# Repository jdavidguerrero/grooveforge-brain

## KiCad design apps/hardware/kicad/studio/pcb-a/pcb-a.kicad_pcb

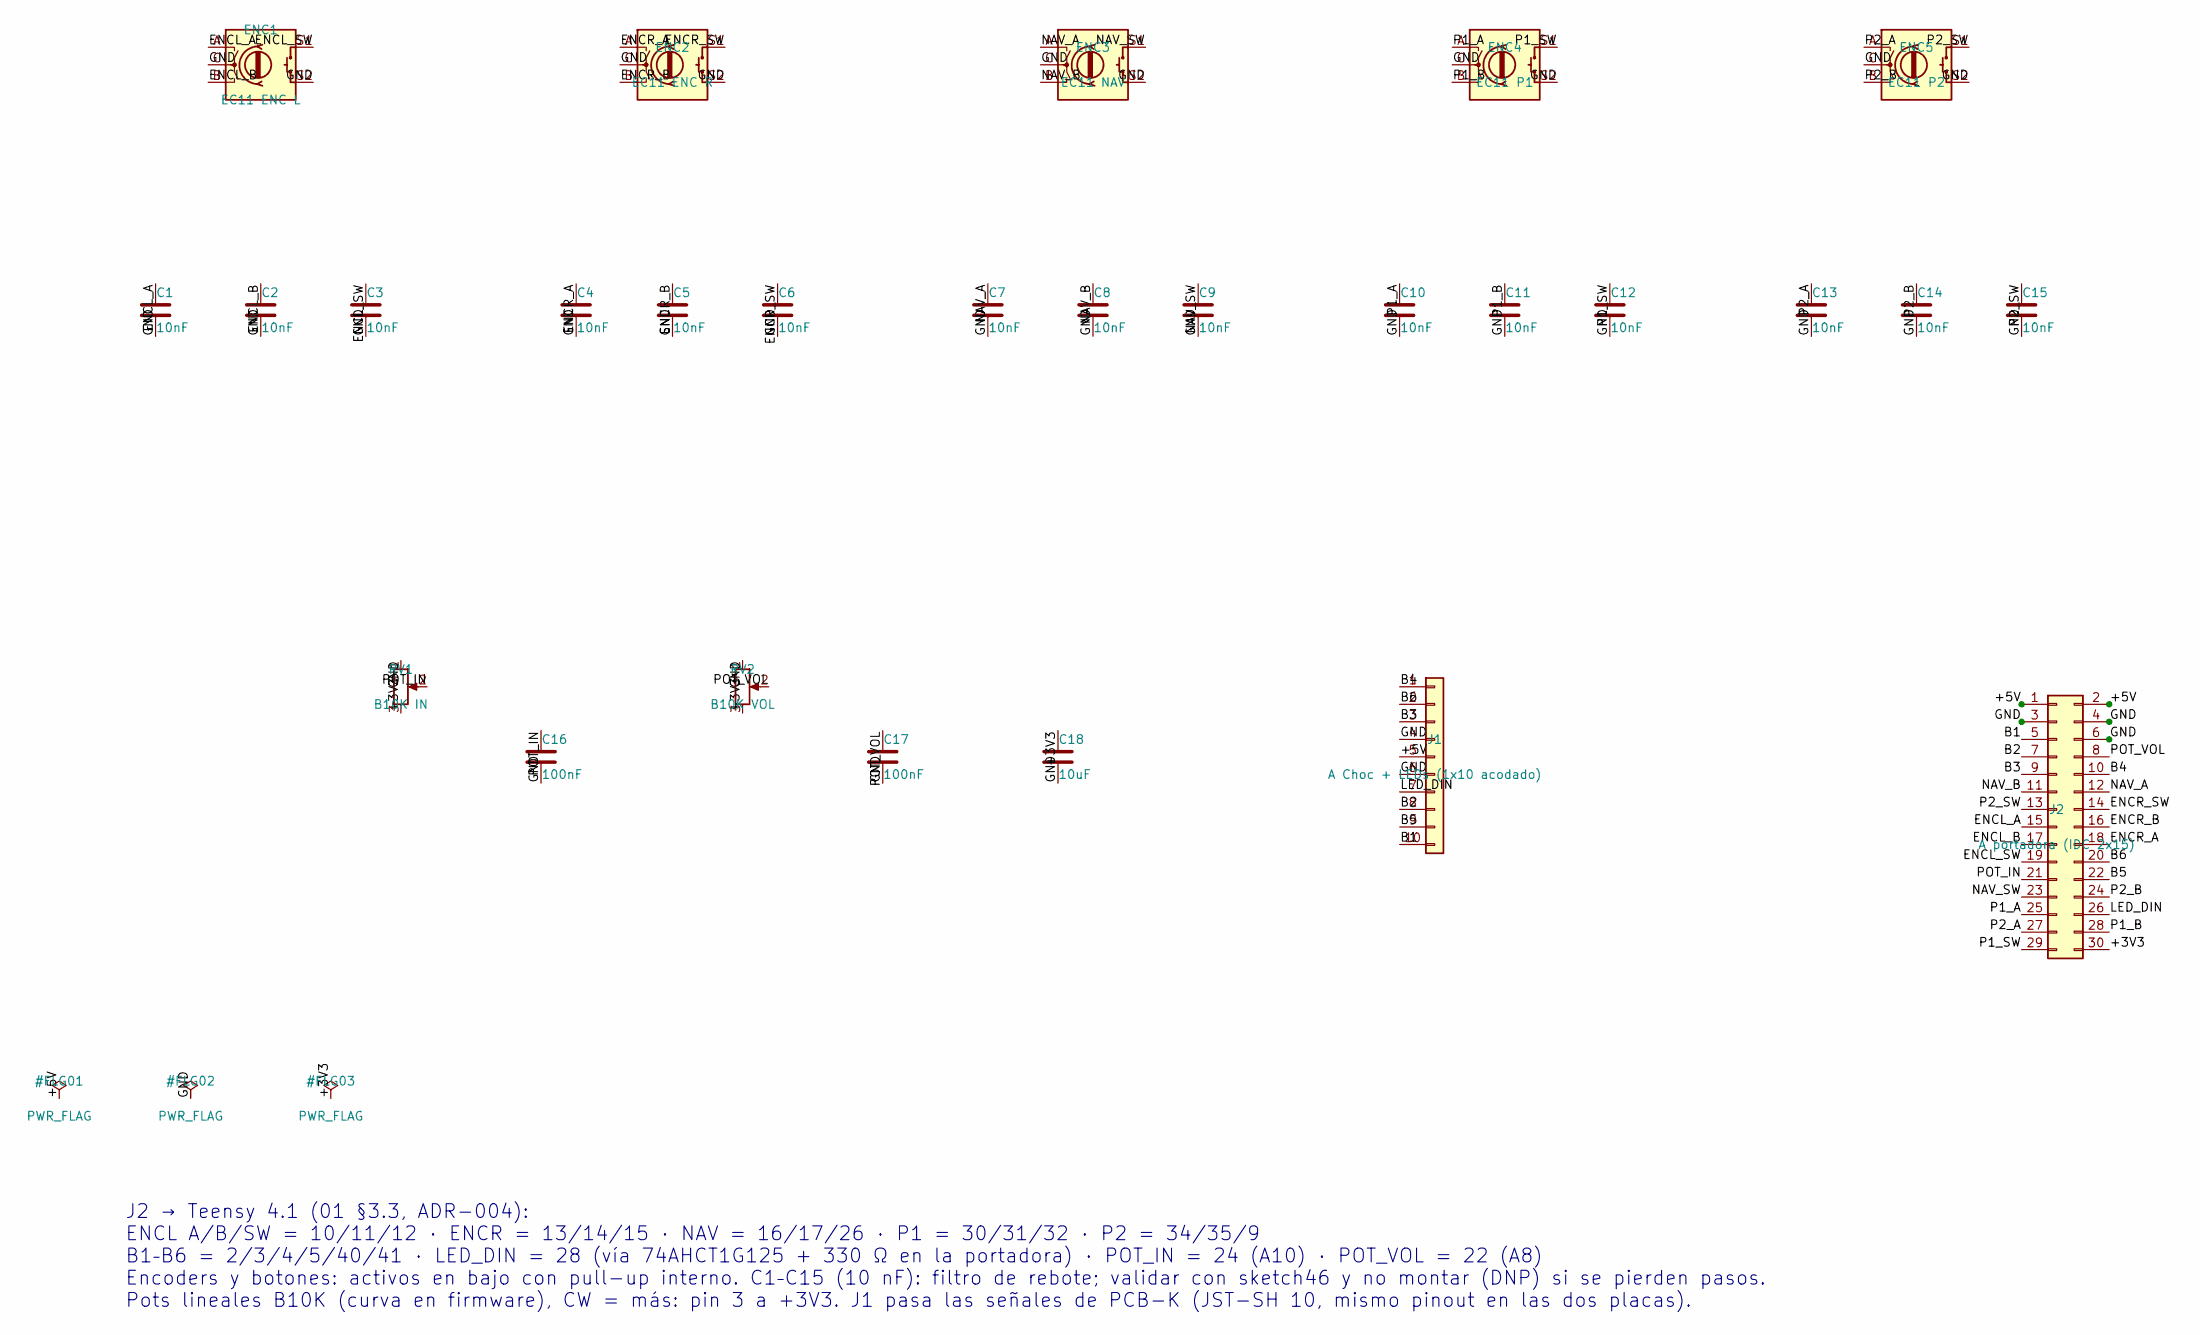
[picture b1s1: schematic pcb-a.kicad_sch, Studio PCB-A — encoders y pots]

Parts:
C1, C2, C3, C4, C5, C6, C7, C8, C9, C10, C11, C12, C13, C14, C15: 10nF; C_0603_1608Metric; LCSC C57112
C16, C17: 100nF; C_0603_1608Metric; LCSC C14663
C18: 10uF; C_0805_2012Metric; LCSC C15850
ENC1: EC11 ENC L; RotaryEncoder_Alps_EC11E-Switch_Vertical_H20mm_MountingHoles
ENC2: EC11 ENC R; RotaryEncoder_Alps_EC11E-Switch_Vertical_H20mm_MountingHoles
ENC3: EC11 NAV; RotaryEncoder_Alps_EC11E-Switch_Vertical_H20mm_MountingHoles
ENC4: EC11 P1; RotaryEncoder_Alps_EC11E-Switch_Vertical_H20mm_MountingHoles
ENC5: EC11 P2; RotaryEncoder_Alps_EC11E-Switch_Vertical_H20mm_MountingHoles
J1: A Choc + LEDs (1x10 acodado); PinHeader_1x10_P2.54mm_Horizontal
J2: A portadora (IDC 2x15); IDC-Header_2x15_P2.54mm_Vertical
RV1: B10K IN; Potentiometer_Alpha_RD901F-40-00D_Single_Vertical
RV2: B10K VOL; Potentiometer_Alpha_RD901F-40-00D_Single_Vertical

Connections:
/+3V3: C18.1, J2.30, RV1.3, RV2.3
/+5V: J1.5, J2.1, J2.2
/B1: J1.10, J2.5
/B2: J1.8, J2.7
/B3: J1.3, J2.9
/B4: J1.1, J2.10
/B5: J1.9, J2.22
/B6: J1.2, J2.20
/ENCL_A: C1.1, ENC1.A, J2.15
/ENCL_B: C2.1, ENC1.B, J2.17
/ENCL_SW: C3.1, ENC1.S1, J2.19
/ENCR_A: C4.1, ENC2.A, J2.18
/ENCR_B: C5.1, ENC2.B, J2.16
/ENCR_SW: C6.1, ENC2.S1, J2.14
/GND: C1.2, C2.2, C3.2, C4.2, C5.2, C6.2, C7.2, C8.2, C9.2, C10.2, C11.2, C12.2, C13.2, C14.2, C15.2, C16.2, C17.2, C18.2, ENC1.C, ENC1.S2, ENC2.C, ENC2.S2, ENC3.C, ENC3.S2, ENC4.C, ENC4.S2, ENC5.C, ENC5.S2, J1.4, J1.6, J2.3, J2.4, J2.6, RV1.1, RV2.1
/LED_DIN: J1.7, J2.26
/NAV_A: C7.1, ENC3.A, J2.12
/NAV_B: C8.1, ENC3.B, J2.11
/NAV_SW: C9.1, ENC3.S1, J2.23
/P1_A: C10.1, ENC4.A, J2.25
/P1_B: C11.1, ENC4.B, J2.28
/P1_SW: C12.1, ENC4.S1, J2.29
/P2_A: C13.1, ENC5.A, J2.27
/P2_B: C14.1, ENC5.B, J2.24
/P2_SW: C15.1, ENC5.S1, J2.13
/POT_IN: C16.1, J2.21, RV1.2
/POT_VOL: C17.1, J2.8, RV2.2

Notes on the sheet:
J2 → Teensy 4.1 (01 §3.3, ADR-004): ENCL A/B/SW = 10/11/12 · ENCR = 13/14/15 · NAV = 16/17/26 · P1 = 30/31/32 · P2 = 34/35/9 B1–B6 = 2/3/4/5/40/41 · LED_DIN = 28 (vía 74AHCT1G125 + 330 Ω en la portadora) · POT_IN = 24 (A10) · POT_VOL = 22 (A8) Encoders y botones: activos en bajo con pull-up interno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

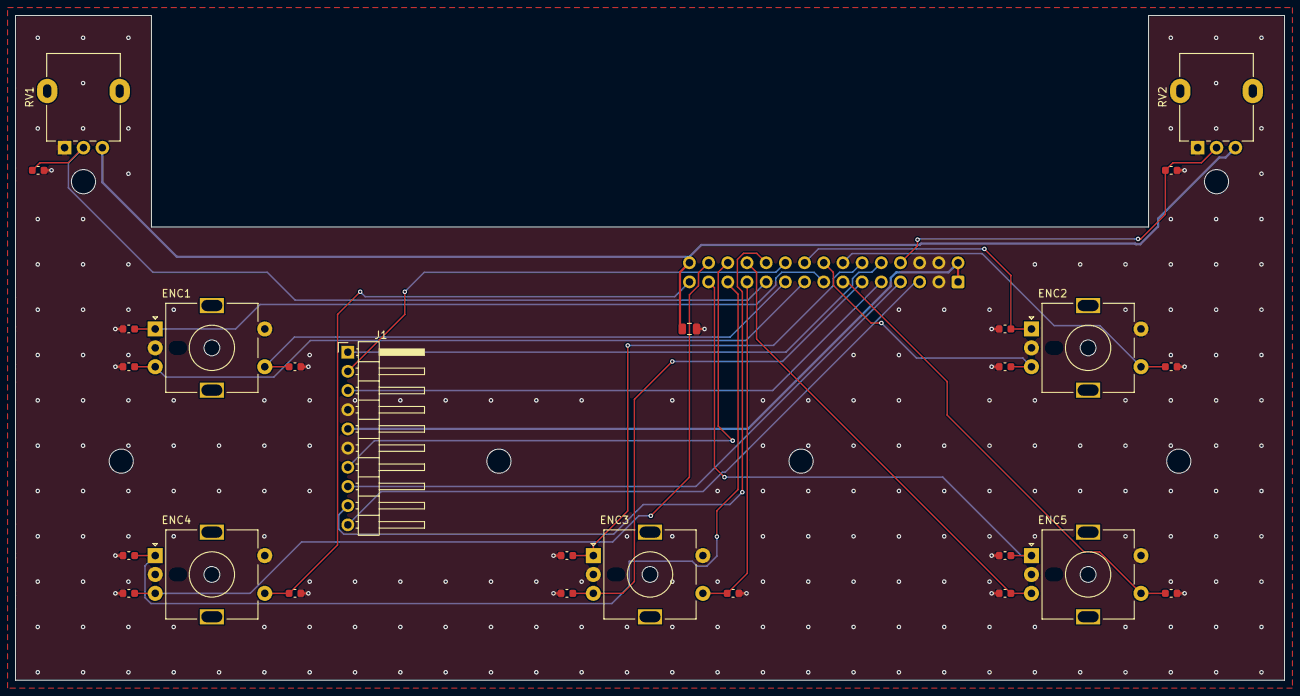
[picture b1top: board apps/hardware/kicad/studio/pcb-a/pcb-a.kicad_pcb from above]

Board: 2 copper layers, 168.0 x 88.0 mm, 27 parts (1 on the bottom side), 27 nets.

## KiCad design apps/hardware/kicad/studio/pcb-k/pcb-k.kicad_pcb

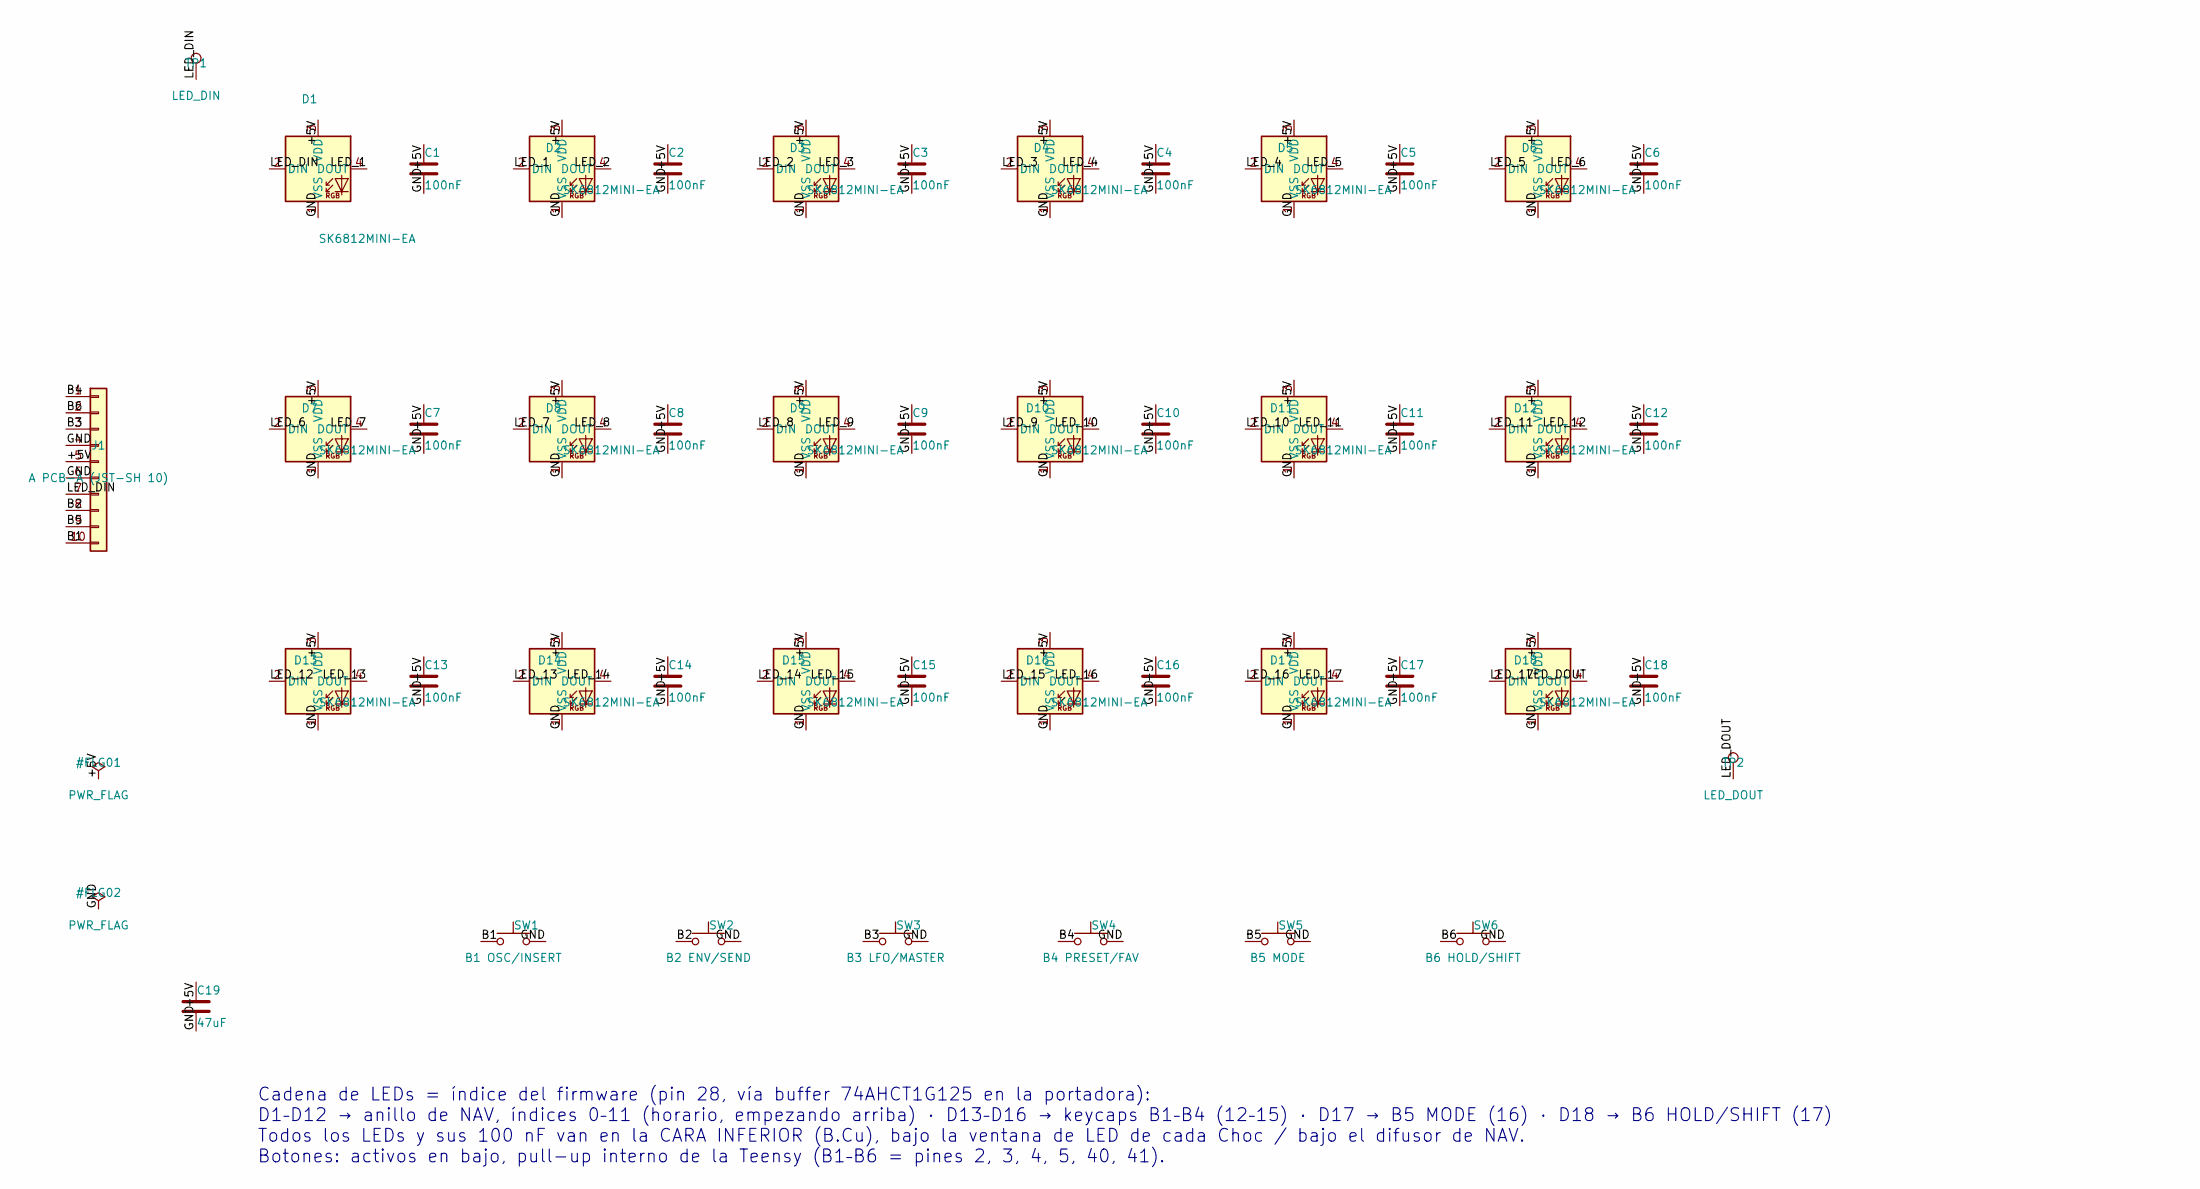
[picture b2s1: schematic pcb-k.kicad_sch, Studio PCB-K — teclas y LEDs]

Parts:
C1, C2, C3, C4, C5, C6, C7, C8, C9, C10, C11, C12, C13, C14, C15, C16, C17, C18: 100nF; C_0603_1608Metric; LCSC C14663
C19: 47uF; C_1206_3216Metric; LCSC C96123
D1, D2, D3, D4, D5, D6, D7, D8, D9, D10, D11, D12, D13, D14, D15, D16, D17, D18: SK6812MINI-EA; LED_SK6812MINI-E_3.2x2.8mm_P1.5mm_ReverseMount; LCSC C5378731
J1: A PCB-A (JST-SH 10); JST_SH_SM10B-SRSS-TB_1x10-1MP_P1.00mm_Horizontal; LCSC C160409
SW1: B1 OSC/INSERT; SW_Kailh_Choc_V2_1u
SW2: B2 ENV/SEND; SW_Kailh_Choc_V2_1u
SW3: B3 LFO/MASTER; SW_Kailh_Choc_V2_1u
SW4: B4 PRESET/FAV; SW_Kailh_Choc_V2_1u
SW5: B5 MODE; SW_Kailh_Choc_V2_1u
SW6: B6 HOLD/SHIFT; SW_Kailh_Choc_V2_1u
TP1: LED_DIN; TestPoint_Pad_D1.0mm
TP2: LED_DOUT; TestPoint_Pad_D1.0mm

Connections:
/+5V: C1.1, C2.1, C3.1, C4.1, C5.1, C6.1, C7.1, C8.1, C9.1, C10.1, C11.1, C12.1, C13.1, C14.1, C15.1, C16.1, C17.1, C18.1, C19.1, D1.3 (VDD), D2.3 (VDD), D3.3 (VDD), D4.3 (VDD), D5.3 (VDD), D6.3 (VDD), D7.3 (VDD), D8.3 (VDD), D9.3 (VDD), D10.3 (VDD), D11.3 (VDD), D12.3 (VDD), D13.3 (VDD), D14.3 (VDD), D15.3 (VDD), D16.3 (VDD), D17.3 (VDD), D18.3 (VDD), J1.5
/B1: J1.10, SW1.1
/B2: J1.8, SW2.1
/B3: J1.3, SW3.1
/B4: J1.1, SW4.1
/B5: J1.9, SW5.1
/B6: J1.2, SW6.1
/GND: C1.2, C2.2, C3.2, C4.2, C5.2, C6.2, C7.2, C8.2, C9.2, C10.2, C11.2, C12.2, C13.2, C14.2, C15.2, C16.2, C17.2, C18.2, C19.2, D1.1 (VSS), D2.1 (VSS), D3.1 (VSS), D4.1 (VSS), D5.1 (VSS), D6.1 (VSS), D7.1 (VSS), D8.1 (VSS), D9.1 (VSS), D10.1 (VSS), D11.1 (VSS), D12.1 (VSS), D13.1 (VSS), D14.1 (VSS), D15.1 (VSS), D16.1 (VSS), D17.1 (VSS), D18.1 (VSS), J1.4, J1.6, SW1.2, SW2.2, SW3.2, SW4.2, SW5.2, SW6.2
/LED_1: D1.4 (DOUT), D2.2 (DIN)
/LED_2: D2.4 (DOUT), D3.2 (DIN)
/LED_3: D3.4 (DOUT), D4.2 (DIN)
/LED_4: D4.4 (DOUT), D5.2 (DIN)
/LED_5: D5.4 (DOUT), D6.2 (DIN)
/LED_6: D6.4 (DOUT), D7.2 (DIN)
/LED_7: D7.4 (DOUT), D8.2 (DIN)
/LED_8: D8.4 (DOUT), D9.2 (DIN)
/LED_9: D9.4 (DOUT), D10.2 (DIN)
/LED_10: D10.4 (DOUT), D11.2 (DIN)
/LED_11: D11.4 (DOUT), D12.2 (DIN)
/LED_12: D12.4 (DOUT), D13.2 (DIN)
/LED_13: D13.4 (DOUT), D14.2 (DIN)
/LED_14: D14.4 (DOUT), D15.2 (DIN)
/LED_15: D15.4 (DOUT), D16.2 (DIN)
/LED_16: D16.4 (DOUT), D17.2 (DIN)
/LED_17: D17.4 (DOUT), D18.2 (DIN)
/LED_DIN: D1.2 (DIN), J1.7, TP1.1
/LED_DOUT: D18.4 (DOUT), TP2.1

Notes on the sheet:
Cadena de LEDs = índice del firmware (pin 28, vía buffer 74AHCT1G125 en la portadora): D1–D12 → anillo de NAV, índices 0–11 (horario, empezando arriba) · D13–D16 → keycaps B1–B4 (12–15) · D17 → B5 MODE (16) · D18 → B6 HOLD/SHIFT (17) Todos los LEDs y sus 100 nF van en la CARA INFERIOR (B.Cu), bajo 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

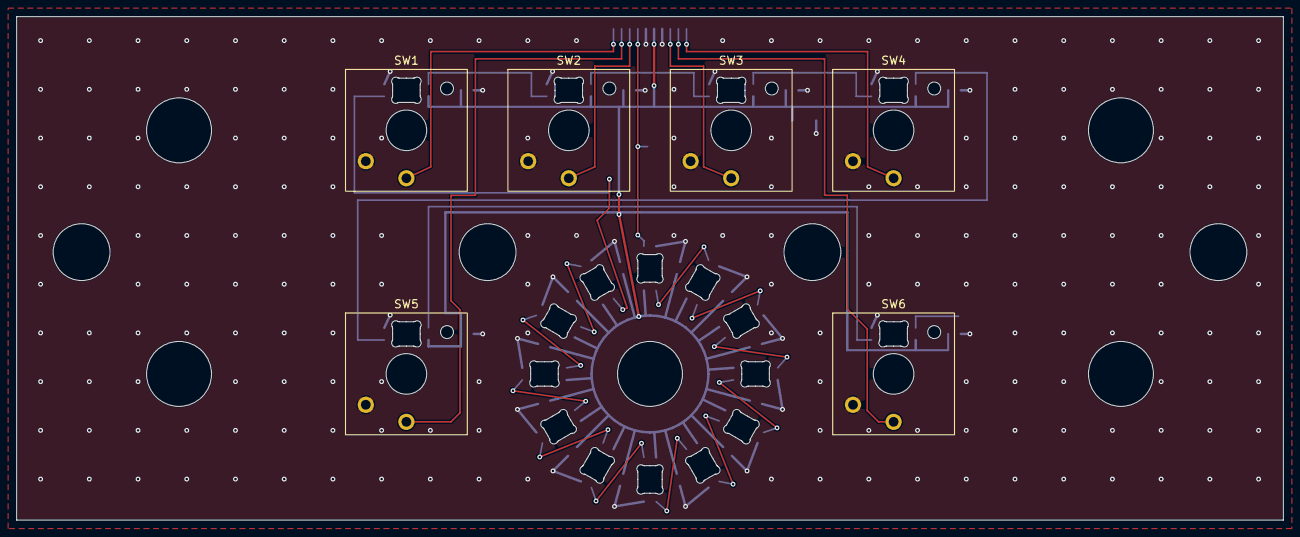
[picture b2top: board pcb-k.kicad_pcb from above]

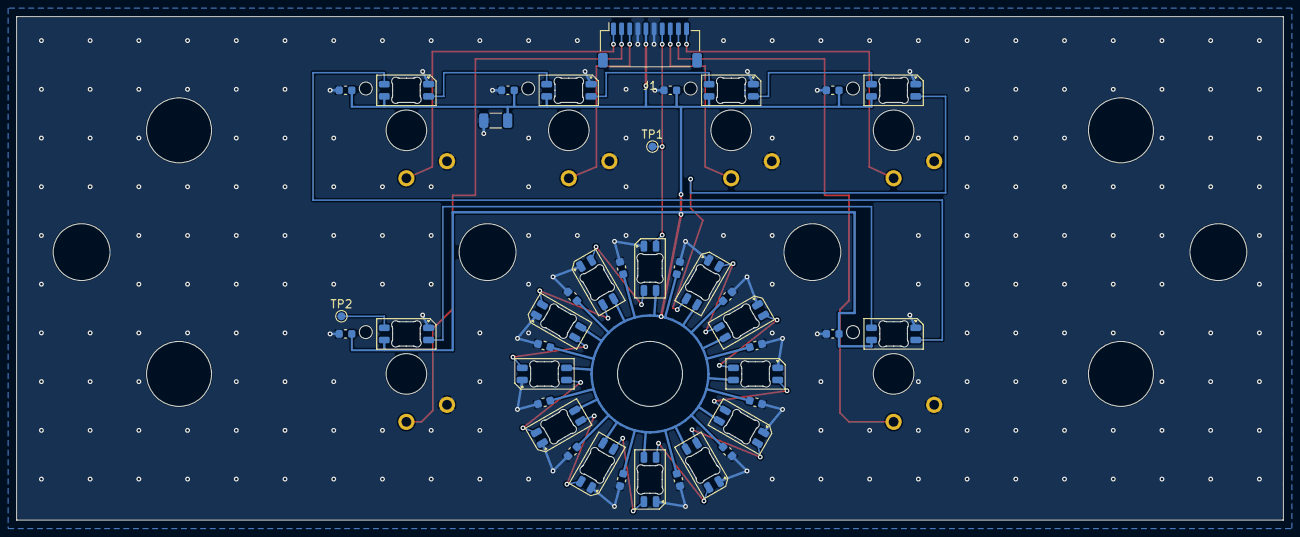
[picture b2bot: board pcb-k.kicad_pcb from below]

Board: 2 copper layers, 156.0 x 62.0 mm, 46 parts (40 on the bottom side), 27 nets.

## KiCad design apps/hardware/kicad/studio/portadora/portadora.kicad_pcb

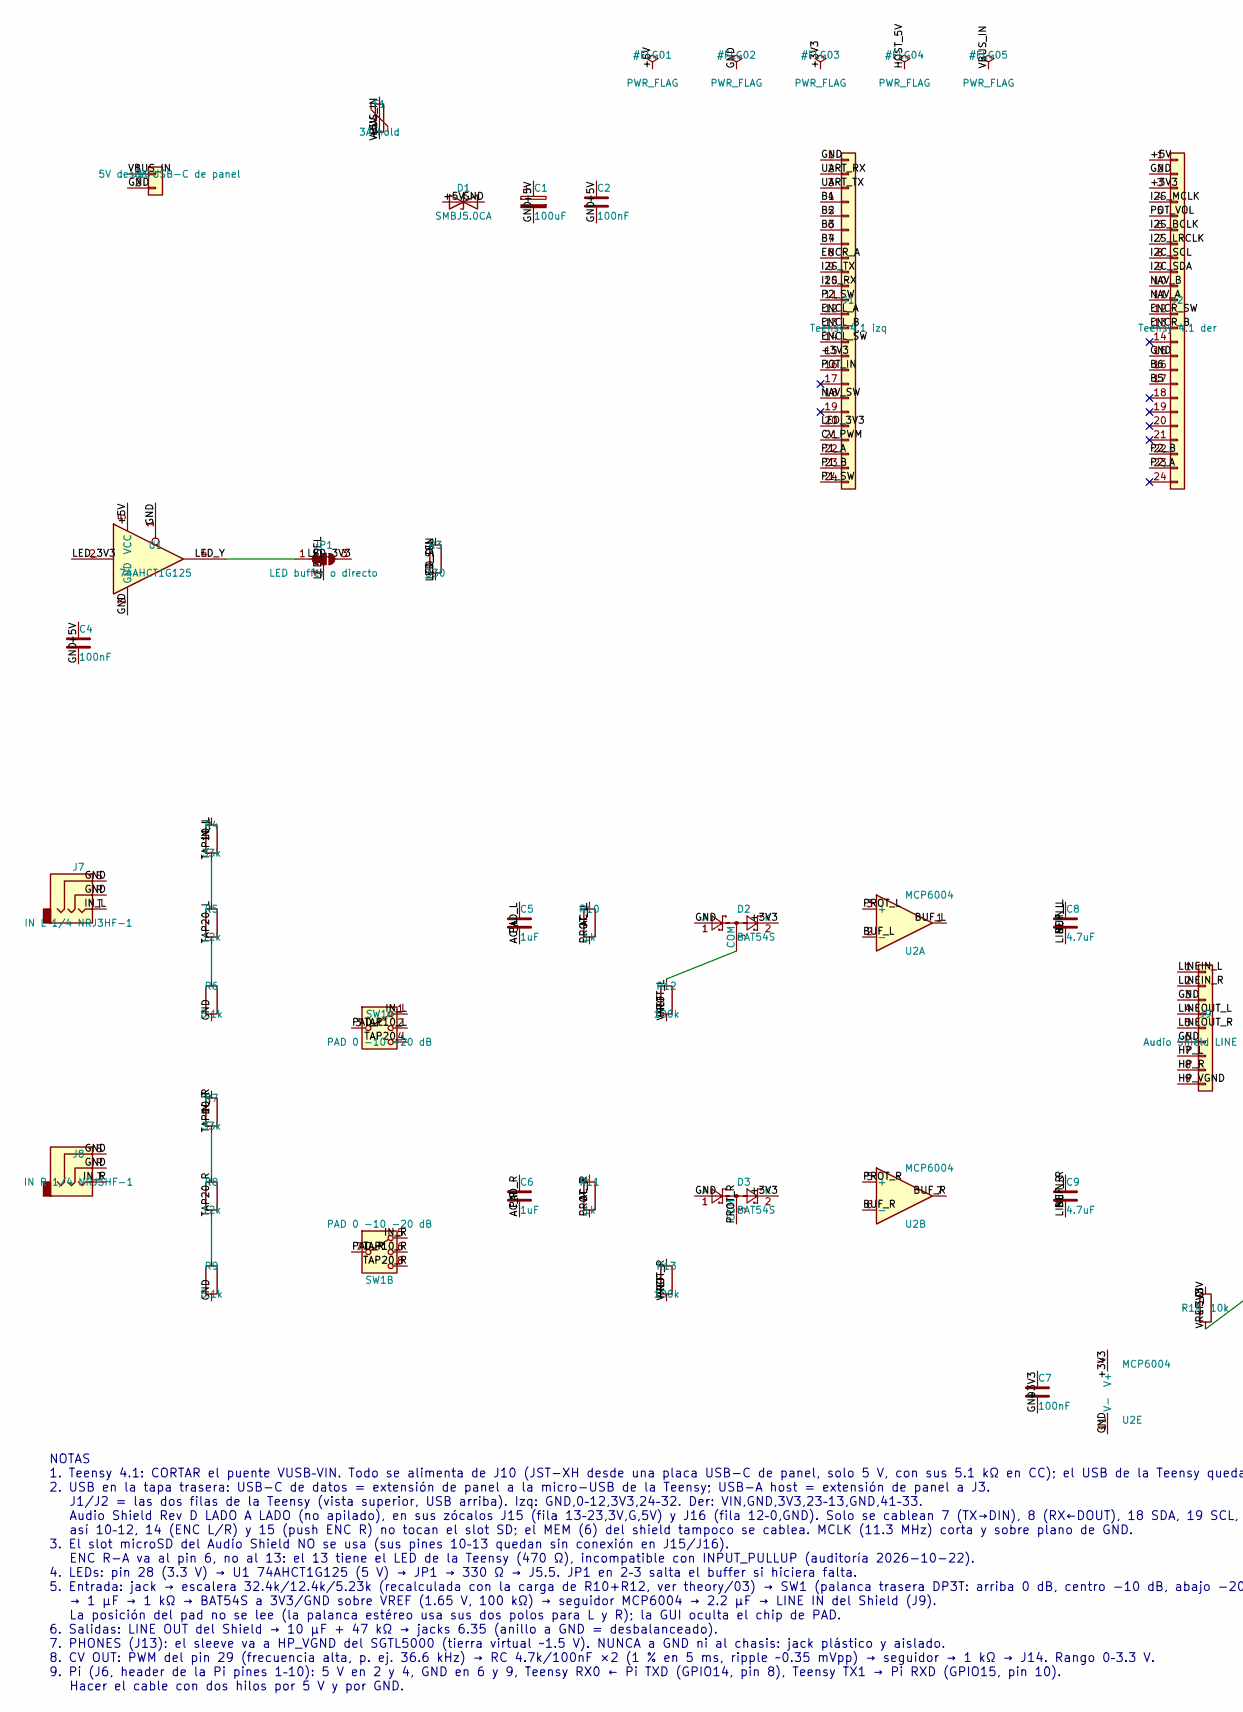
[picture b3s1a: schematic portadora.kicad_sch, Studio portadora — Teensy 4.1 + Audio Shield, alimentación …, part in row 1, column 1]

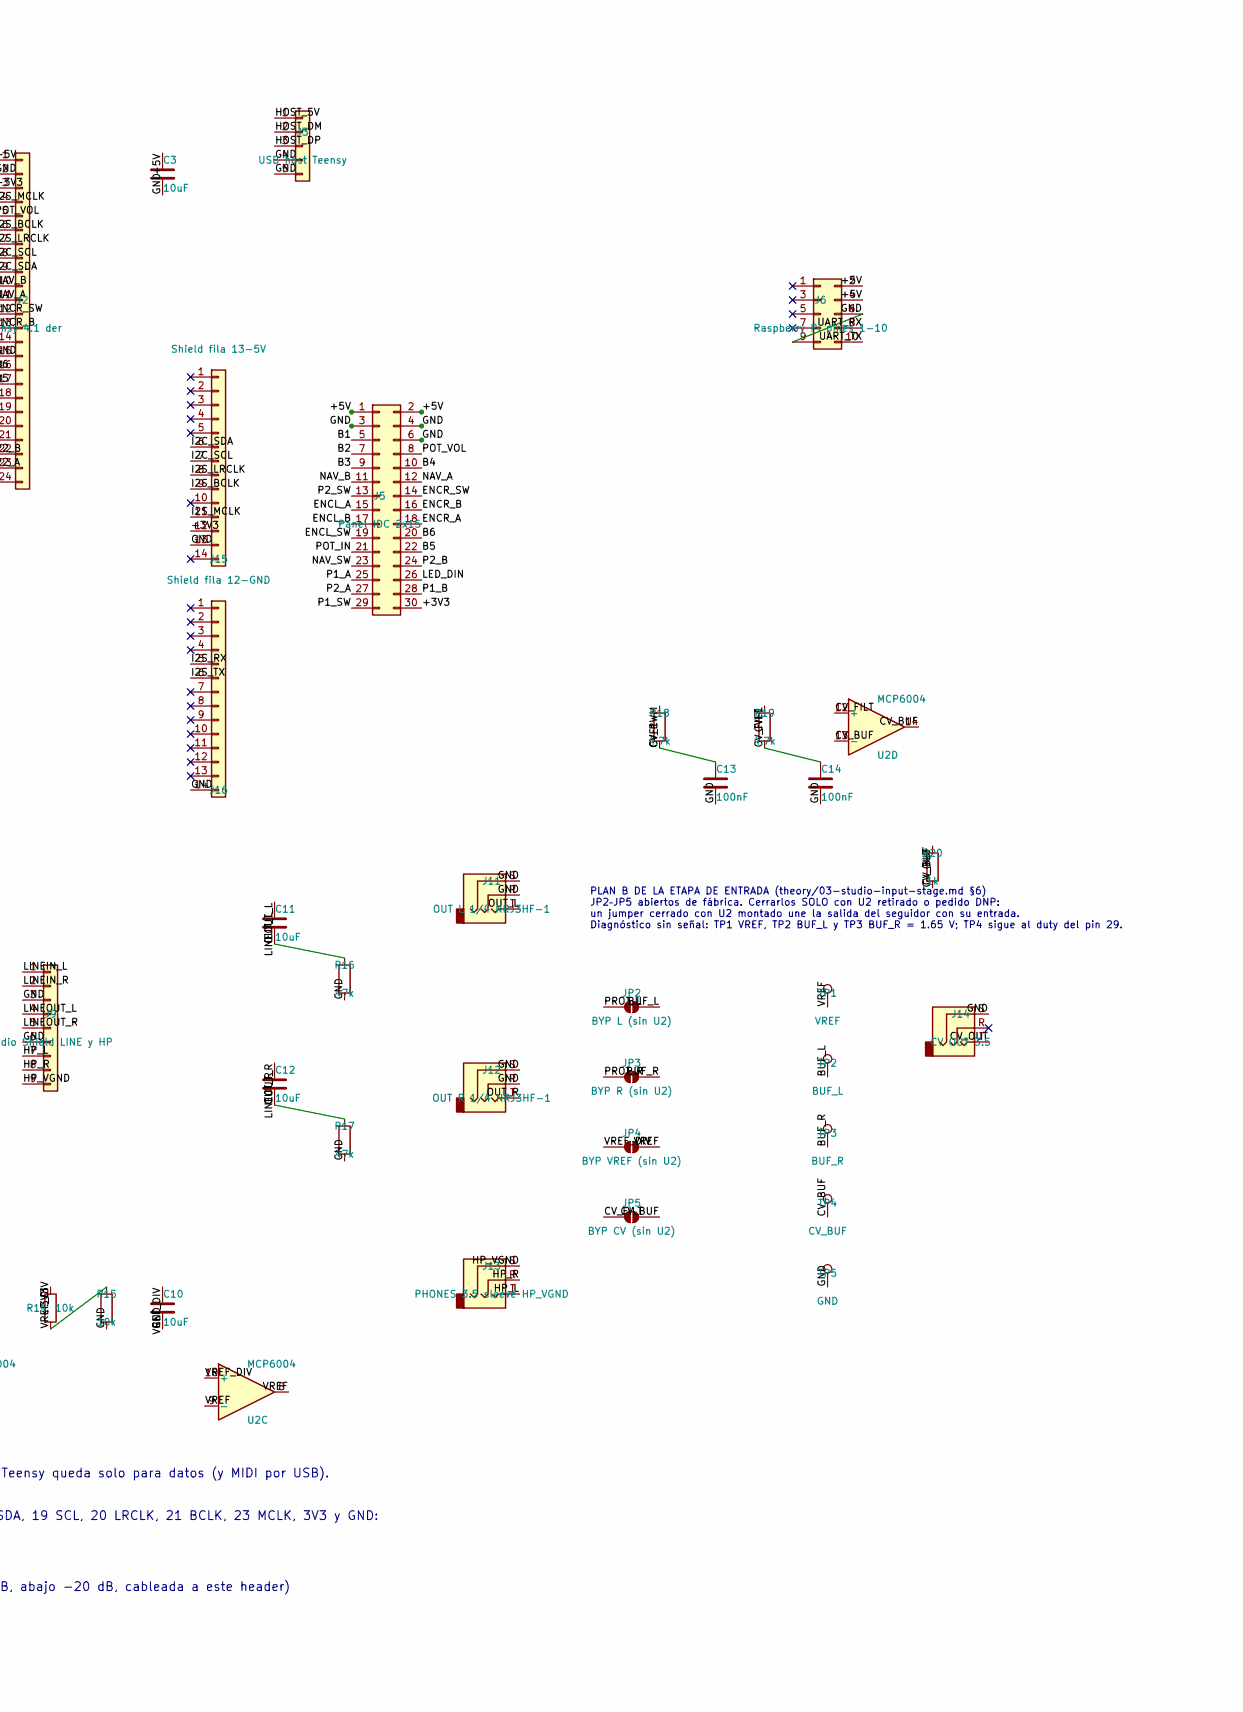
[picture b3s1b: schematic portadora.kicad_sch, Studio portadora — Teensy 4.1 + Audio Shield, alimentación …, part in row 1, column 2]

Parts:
C1: 100uF; CP_Elec_6.3x7.7; LCSC C2992605
C2, C4, C7, C13, C14: 100nF; C_0603_1608Metric; LCSC C14663
C3, C10, C11, C12: 10uF; C_0805_2012Metric; LCSC C15850
C5, C6: 1uF; C_0805_2012Metric; LCSC C28323
C8, C9: 4.7uF; C_0805_2012Metric; LCSC C1779
D1: SMBJ5.0CA; D_SMB; LCSC C113975
D2, D3: BAT54S; SOT-23; LCSC C7420333
F1: 3A hold; Fuse_1812_4532Metric; LCSC C69689
J1: Teensy 4.1 izq; PinSocket_1x24_P2.54mm_Vertical
J2: Teensy 4.1 der; PinSocket_1x24_P2.54mm_Vertical
J3: USB host Teensy; PinHeader_1x05_P2.54mm_Vertical
J5: Panel IDC 2x15; IDC-Header_2x15_P2.54mm_Vertical
J6: Raspberry Pi pines 1-10; IDC-Header_2x05_P2.54mm_Vertical
J7: IN L 1/4 NRJ3HF-1; Jack_6.35mm_Neutrik_NRJ3HF-1_Horizontal
J8: IN R 1/4 NRJ3HF-1; Jack_6.35mm_Neutrik_NRJ3HF-1_Horizontal
J9: Audio Shield LINE y HP; PinHeader_1x09_P2.54mm_Vertical
J10: 5V desde USB-C de panel; JST_XH_B2B-XH-A_1x02_P2.50mm_Vertical
J11: OUT L 1/4 NRJ3HF-1; Jack_6.35mm_Neutrik_NRJ3HF-1_Horizontal
J12: OUT R 1/4 NRJ3HF-1; Jack_6.35mm_Neutrik_NRJ3HF-1_Horizontal
J13: PHONES 3.5 sleeve HP_VGND; Jack_3.5mm_CUI_SJ1-3533NG_Horizontal
J14: CV OUT 3.5; Jack_3.5mm_CUI_SJ1-3533NG_Horizontal
J15: Shield fila 13-5V; PinSocket_1x14_P2.54mm_Vertical
J16: Shield fila 12-GND; PinSocket_1x14_P2.54mm_Vertical
JP1: LED buffer o directo; SolderJumper-3_P1.3mm_Bridged12_RoundedPad1.0x1.5mm
JP2: BYP L (sin U2); SolderJumper-2_P1.3mm_Open_RoundedPad1.0x1.5mm
JP3: BYP R (sin U2); SolderJumper-2_P1.3mm_Open_RoundedPad1.0x1.5mm
JP4: BYP VREF (sin U2); SolderJumper-2_P1.3mm_Open_RoundedPad1.0x1.5mm
JP5: BYP CV (sin U2); SolderJumper-2_P1.3mm_Open_RoundedPad1.0x1.5mm
R3: 330; R_0603_1608Metric; LCSC C23138
R4, R7: 33k; R_0603_1608Metric; LCSC C4216
R5, R8: 12k; R_0603_1608Metric; LCSC C22790
R6, R9: 5.1k; R_0603_1608Metric; LCSC C23186
R10, R11, R20: 1k; R_0603_1608Metric; LCSC C21190
R12, R13: 100k; R_0603_1608Metric; LCSC C25803
R14, R15: 10k; R_0603_1608Metric; LCSC C25804
R16, R17: 47k; R_0603_1608Metric; LCSC C25819
R18, R19: 4.7k; R_0603_1608Metric; LCSC C23162
SW1: PAD 0 -10 -20 dB; PinHeader_2x04_P2.54mm_Vertical
TP1: VREF; TestPoint_Pad_D1.5mm
TP2: BUF_L; TestPoint_Pad_D1.5mm
TP3: BUF_R; TestPoint_Pad_D1.5mm
TP4: CV_BUF; TestPoint_Pad_D1.5mm
TP5: GND; TestPoint_Pad_D1.5mm
U1: 74AHCT1G125; SOT-23-5; LCSC C842287
U2: MCP6004; SOIC-14_3.9x8.7mm_P1.27mm; LCSC C7378

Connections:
/+3V3: C7.1, D2.2 (K), D3.2 (K), J1.15, J2.3, J5.30, J15.12, R14.1, U2.4 (V+)
/+5V: C1.1, C2.1, C3.1, C4.1, D1.1 (A1), F1.2, J2.1, J5.1, J5.2, J6.2, J6.4, U1.5 (VCC)
/AC_L: C5.2, R10.1
/AC_R: C6.2, R11.1
/B1: J1.4, J5.5
/B2: J1.5, J5.7
/B3: J1.6, J5.9
/B4: J1.7, J5.10
/B5: J2.17, J5.22
/B6: J2.16, J5.20
/BUF_L: C8.1, JP2.2 (B), TP2.1, U2.1, U2.2 (-)
/BUF_R: C9.1, JP3.2 (B), TP3.1, U2.6 (-), U2.7
/CVF1: C13.1, R18.2, R19.1
/CV_BUF: JP5.2 (B), R20.1, TP4.1, U2.13 (-), U2.14
/CV_FILT: C14.1, JP5.1 (A), R19.2, U2.12 (+)
/CV_OUT: J14.T, R20.2
/CV_PWM: J1.21, R18.1
/ENCL_A: J1.12, J5.15
/ENCL_B: J1.13, J5.17
/ENCL_SW: J1.14, J5.19
/ENCR_A: J1.8, J5.18
/ENCR_B: J2.13, J5.16
/ENCR_SW: J2.12, J5.14
/GND: C1.2, C2.2, C3.2, C4.2, C7.2, C10.2, C13.2, C14.2, D1.2 (A2), D2.1 (A), D3.1 (A), J1.1, J2.2, J2.15, J3.4, J3.5, J5.3, J5.4, J5.6, J6.6, J6.9, J7.R, J7.S, J8.R, J8.S, J9.3, J9.6, J10.2, J11.R, J11.S, J12.R, J12.S, J14.S, J15.13, J16.14, R6.2, R9.2, R15.2, R16.2, R17.2, TP5.1, U1.1, U1.3 (GND), U2.11 (V-)
/HOST_5V: J3.1
/HOST_DM: J3.2
/HOST_DP: J3.3
/HP_L: J9.7, J13.T
/HP_R: J9.8, J13.R
/HP_VGND: J9.9, J13.S
/I2C_SCL: J2.8, J15.7
/I2C_SDA: J2.9, J15.6
/I2S_BCLK: J2.6, J15.9
/I2S_LRCLK: J2.7, J15.8
/I2S_MCLK: J2.4, J15.11
/I2S_RX: J1.10, J16.5
/I2S_TX: J1.9, J16.6
/IN_L: J7.T, R4.1, SW1.1
/IN_R: J8.T, R7.1, SW1.5
/LED_3V3: J1.20, JP1.3 (B), U1.2
/LED_DIN: J5.26, R3.2
/LED_SEL: JP1.2 (C), R3.1
/LED_Y: JP1.1 (A), U1.4
/LINEIN_L: C8.2, J9.1
/LINEIN_R: C9.2, J9.2
/LINEOUT_L: C11.1, J9.4
/LINEOUT_R: C12.1, J9.5
/NAV_A: J2.11, J5.12
/NAV_B: J2.10, J5.11
/NAV_SW: J1.18, J5.23
/OUT_L: C11.2, J11.T, R16.1
/OUT_R: C12.2, J12.T, R17.1
/P1_A: J1.22, J5.25
/P1_B: J1.23, J5.28
/P1_SW: J1.24, J5.29
/P2_A: J2.23, J5.27
/P2_B: J2.22, J5.24
/P2_SW: J1.11, J5.13
/PAD_L: C5.1, SW1.3
/PAD_R: C6.1, SW1.7
/POT_IN: J1.16, J5.21
/POT_VOL: J2.5, J5.8
/PROT_L: D2.3 (COM), JP2.1 (A), R10.2, R12.1, U2.3 (+)
/PROT_R: D3.3 (COM), JP3.1 (A), R11.2, R13.1, U2.5 (+)
/TAP10_L: R4.2, R5.1, SW1.2
/TAP10_R: R7.2, R8.1, SW1.6
/TAP20_L: R5.2, R6.1, SW1.4
/TAP20_R: R8.2, R9.1, SW1.8
/UART_RX: J1.2, J6.8
/UART_TX: J1.3, J6.10
/VBUS_IN: F1.1, J10.1
/VREF: JP4.2 (B), R12.2, R13.2, TP1.1, U2.8, U2.9 (-)
/VREF_DIV: C10.1, JP4.1 (A), R14.2, R15.1, U2.10 (+)

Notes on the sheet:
NOTAS 1. Teensy 4.1: CORTAR el puente VUSB–VIN. Todo se alimenta de J10 (JST-XH desde una placa USB-C de panel, solo 5 V, con sus 5.1 kΩ en CC); el USB de la Teensy queda solo para datos (y MIDI por USB). 2. USB en la tapa trasera: USB-C de datos = extensión de panel a la micro-USB de la Teensy; US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
PLAN B DE LA ETAPA DE ENTRADA (theory/03-studio-input-stage.md §6) JP2–JP5 abiertos de fábrica. Cerrarlos SOLO con U2 retirado o pedido DNP: un jumper cerrado con U2 montado une la salida del seguidor con su entrada. Diagnóstico sin señal: TP1 VREF, TP2 BUF_L y TP3 BUF_R = 1.65 V; TP4 sigue al duty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

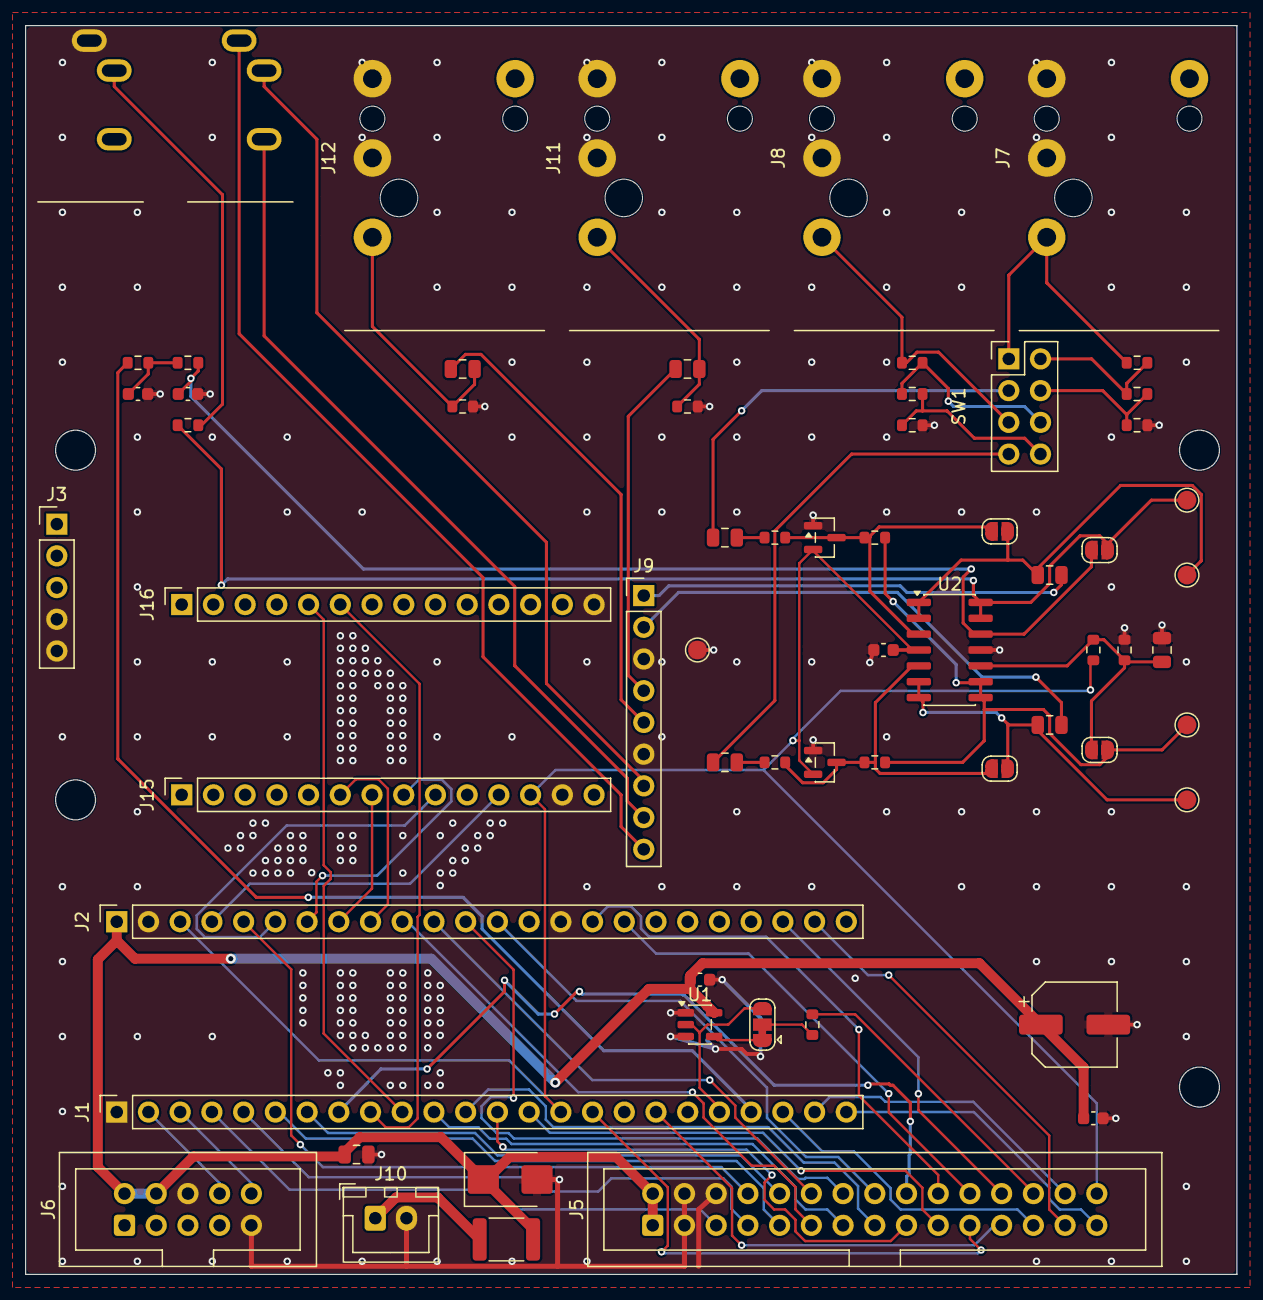
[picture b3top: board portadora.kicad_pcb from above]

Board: 2 copper layers, 97.0 x 100.0 mm, 64 parts (0 on the bottom side), 70 nets.
